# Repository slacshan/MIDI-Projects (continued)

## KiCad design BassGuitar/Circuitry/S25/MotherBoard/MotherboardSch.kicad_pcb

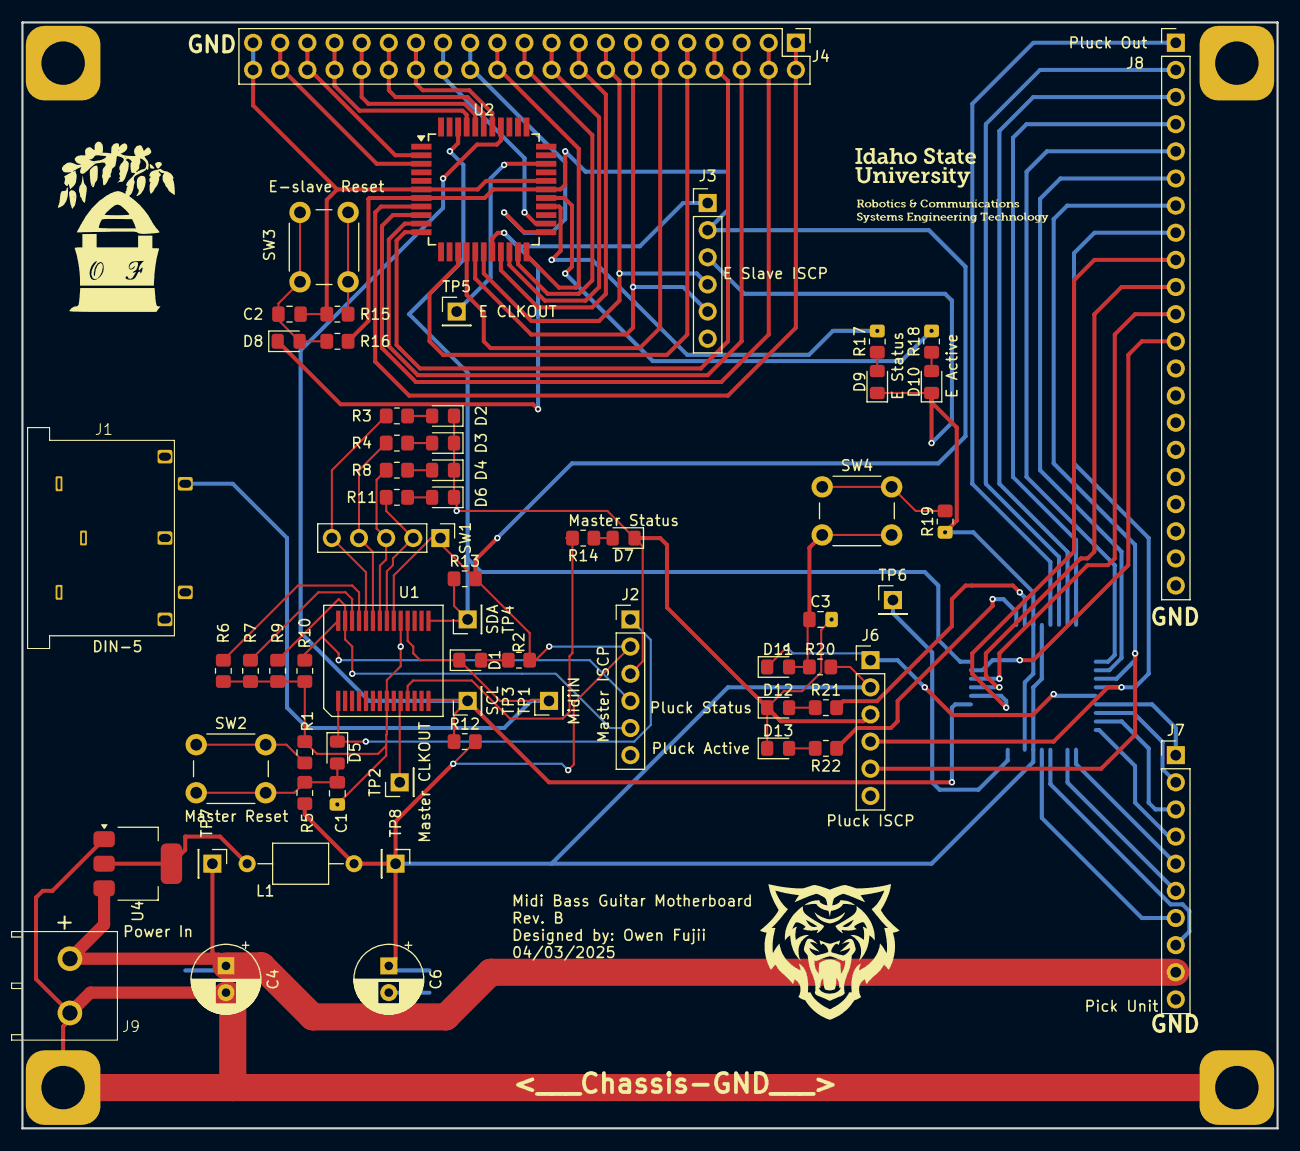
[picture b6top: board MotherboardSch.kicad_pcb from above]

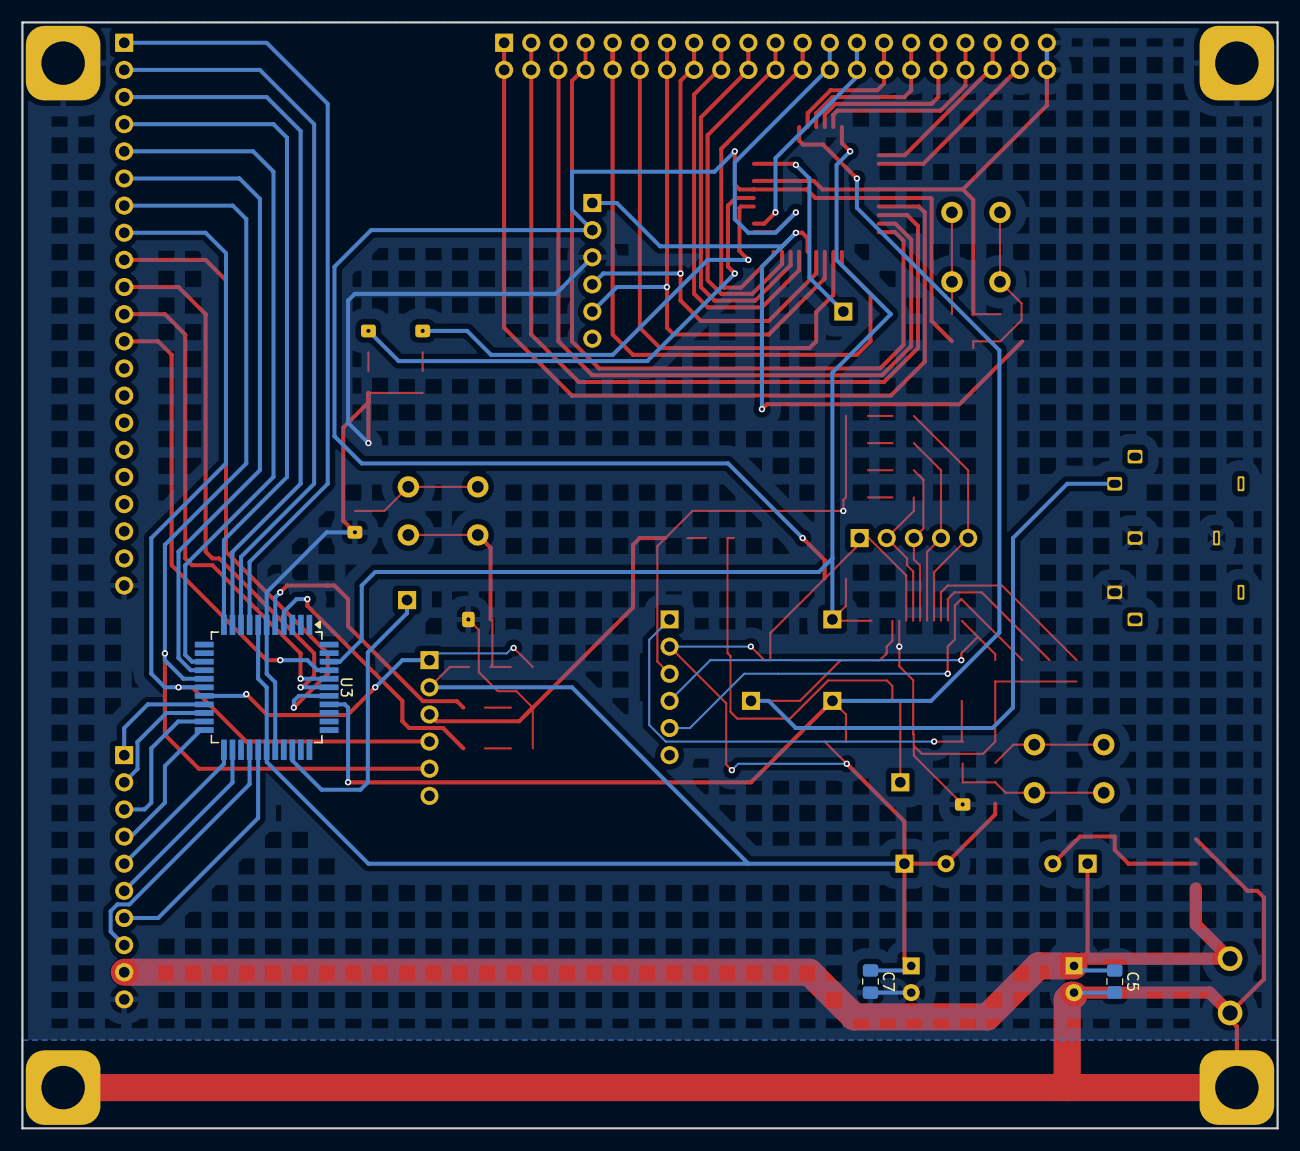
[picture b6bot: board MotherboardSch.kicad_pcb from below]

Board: 2 copper layers, 117.5 x 103.5 mm, 67 parts (3 on the bottom side), 83 nets.

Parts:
C1, C2, C3: 10uF; C_0805_2012Metric_Pad1.18x1.45mm_HandSolder
C4, C6: 100uF; CP_Radial_D6.3mm_P2.50mm
C5, C7: 0.1uF; C_0805_2012Metric_Pad1.18x1.45mm_HandSolder
D1: LED; D_0805_2012Metric_Pad1.15x1.40mm_HandSolder
D2: 8; D_0805_2012Metric_Pad1.15x1.40mm_HandSolder
D3: 4; D_0805_2012Metric_Pad1.15x1.40mm_HandSolder
D4: 2; D_0805_2012Metric_Pad1.15x1.40mm_HandSolder
D5, D8, D11: 4148; D_0805_2012Metric_Pad1.15x1.40mm_HandSolder
D6: 1; D_0805_2012Metric_Pad1.15x1.40mm_HandSolder
D7: Master Status; D_0805_2012Metric_Pad1.15x1.40mm_HandSolder
D9: E Status; D_0805_2012Metric_Pad1.15x1.40mm_HandSolder
D10: E Active; D_0805_2012Metric_Pad1.15x1.40mm_HandSolder
D12: Pluck Status; D_0805_2012Metric_Pad1.15x1.40mm_HandSolder
D13: Pluck Active; D_0805_2012Metric_Pad1.15x1.40mm_HandSolder
J1: DIN-5; Din_5 Connector
J2: Master ISCP; PinHeader_1x06_P2.54mm_Vertical
J3: E SLAVE ISCP; PinHeader_1x06_P2.54mm_Vertical
J4: E Slave Out; PinHeader_2x21_P2.54mm_Vertical
J6: Pluck ISCP; PinHeader_1x06_P2.54mm_Vertical
J7: Pick Unit; PinHeader_1x10_P2.54mm_Vertical
J8: Pluck Out; PinHeader_1x21_P2.54mm_Vertical
J9: Power In; Two_Pin_Screw_Terminal
L1: 10uH; L_Axial_L5.0mm_D3.6mm_P10.00mm_Horizontal_Murata_BL01RN1A2A2
R1, R15, R19: 10Ω; R_0805_2012Metric_Pad1.20x1.40mm_HandSolder
R2: 1kΩ; R_0805_2012Metric_Pad1.20x1.40mm_HandSolder
R3, R4, R8, R11, R14, R17, R18, R21, R22: 330Ω; R_0805_2012Metric_Pad1.20x1.40mm_HandSolder
R5, R6, R7, R9, R10, R16, R20: 10kΩ; R_0805_2012Metric_Pad1.20x1.40mm_HandSolder
R12, R13: 2.2kΩ; R_0805_2012Metric_Pad1.20x1.40mm_HandSolder
SW1: PinHeader_1x05_P2.54mm_Vertical
SW2: Master Reset; SW_PUSH_6mm_H5mm
SW3: E-slave Reset; SW_PUSH_6mm_H5mm
SW4: Pluck Reset; SW_PUSH_6mm_H5mm
TP1: MidiIN; PinHeader_1x01_P2.54mm_Vertical
TP2: Master CLKOUT; PinHeader_1x01_P2.54mm_Vertical
TP3: SCL; PinHeader_1x01_P2.54mm_Vertical
TP4: SDA; PinHeader_1x01_P2.54mm_Vertical
TP5: E CLKOUT; PinHeader_1x01_P2.54mm_Vertical
TP6: PLUCK CLKOUT; PinHeader_1x01_P2.54mm_Vertical
TP7: P-IN; PinHeader_1x01_P2.54mm_Vertical
TP8: 5v; PinHeader_1x01_P2.54mm_Vertical
U1: PIC16F1788; SSOP-28
U2, U3: PIC16F1789; TQFP-44_10x10mm_P0.8mm_Handsolder
U4: LM1117MP-1.8; SOT-223-3_TabPin2

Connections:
1: R11.2, SW1.2 (1), U1.21 (INT/AN12/RB0)
2: R8.2, SW1.3 (2), U1.22 (P1C/AN10/RB1)
4: R4.2, SW1.4, U1.23 (P1B/AN8/RB2)
8: R3.2, SW1.5 (8), U1.24 (PGM/C12IN2-/AN8/RB3)
+5v: C6.1, C7.1, J2.2, J3.2, J6.2, L1.2, R2.2, R5.2, R12.2, R13.2, R16.2, R20.2, SW1.1 (Com), TP8.1, U1.20 (VDD), U2.7 (Vdd), U2.28 (Vdd), U3.7 (Vdd), U3.28 (Vdd)
+12v: C4.1, C5.1, J7.9, J9.1, TP7.1, U4.3 (VI)
/String Strike Slave/A0: J8.3, U3.10 (RB2/AN8/OPA2IN-/DAC3OUT1)
/String Strike Slave/A1: J8.4, U3.11 (RB3/AN9/CXNI2-/CCP2)
/String Strike Slave/A MUTE: J8.10, U3.39 (RD1/CxIN4-/OPA3OUT)
/String Strike Slave/D0: J8.5, U3.14 (RB4/AN11/C3IN1+)
/String Strike Slave/D1: J8.6, U3.15 (RB5/AN13/C4IN2-/CCP3)
/String Strike Slave/D MUTE: J8.11, U3.40 (RD2/OPA3IN-/DAC4OUT1)
/String Strike Slave/E0: J8.1, U3.8 (RB0/AN12/CCP1/C2IN1+)
/String Strike Slave/E1: J8.2, U3.9 (RB1/AN10/CxIN3-/OPA2OUT)
/String Strike Slave/E MUTE: J8.9, U3.38 (RD0/OPA3IN+)
/String Strike Slave/G MUTE: J8.12, U3.41 (RD3/PSMC4A)
A1: J4.5, U2.14 (RB4/AN11/C3IN1+)
A2: J4.17, U2.40 (RD2/OPA3IN-/DAC4OUT1)
A#1: J4.6, U2.15 (RB5/AN13/C4IN2-/CCP3)
A#2: J4.18, U2.41 (RD3/PSMC4A)
B1: J3.5, J4.7, U2.16 (RB6/C4IN1+/ICSPCLK)
B2: J4.19, U2.2 (RD4/PSM3F)
C2: J3.4, J4.8, U2.17 (RB7/DACxOUT2-/ICSPDAT)
C3: J4.20, U2.3 (RD5/PSMC3E)
C#2: J4.9, U2.19 (RA0/AN0/CxIN0-)
D2: J4.10, U2.20 (RA1/AN1/CxIN1-/OPA1OUT)
D#2: J4.11, U2.21 (RA2/AN2/CxIN0+/DAC1OUT1)
E2: J4.12, U2.22 (RA3/AN3/VREF+/C1IN1+)
Earth_GND: C4.2, C5.2, J9.2, U4.1 (GND)
F1: J4.1, U2.8 (RB0/AN12/CCP1/C2IN1+)
F2: J4.13, U2.23 (RA4/C1OUT/OPA1IN+/T0CKI)
F#1: J4.2, U2.9 (RB1/AN10/CxIN3-/OPA2OUT)
F#2: J4.14, U2.24 (RA5/AN4/C2OUT/OPA1IN+)
G1: J4.3, U2.10 (RB2/AN8/OPA2IN-/DAC3OUT1)
G2: J4.15, U2.38 (RD0/OPA3IN+)
G#1: J4.4, U2.11 (RB3/AN9/CXNI2-/CCP2)
G#2: J4.16, U2.39 (RD1/CxIN4-/OPA3OUT)
GND: C1.2, C2.2, C3.2, C6.2, C7.2, D2.1 (K), D3.1 (K), D4.1 (K), D6.1 (K), D7.1 (K), D9.1 (K), D10.1 (K), D12.1 (K), D13.1 (K), J1.2, J1.4, J1.6, J2.3, J3.3, J4.21, J6.3, J7.10, J8.21, R1.1, R6.1, R7.1, R9.1, R10.1, R15.1, R19.1, U1.8 (VSS), U1.19 (VSS), U2.6 (Vss), U2.29 (Vss), U3.6 (Vss), U3.29 (Vss)
I2Cclk: R12.1, TP3.1, U1.14 (RC3/SCK/SCL), U2.37 (RC3/SCL/SCK/PSMC1D), U3.37 (RC3/SCL/SCK/PSMC1D)
I2Cdat: R13.1, TP4.1, U1.15 (RC4/SDI/SDA), U2.42 (RC4/SDI/SDA/PSMC1E), U3.42 (RC4/SDI/SDA/PSMC1E)
MSCLR E: D8.1, J3.1, U2.18 (Vpp/~MCLR/RE3)
MSCLR P: D11.1, J6.1, U3.18 (Vpp/~MCLR/RE3)
unnamed: C1.1, D5.2, R5.1, SW2.2
unnamed: C2.1, D8.2, R16.1, SW3.2
unnamed: C3.1, D11.2, R20.1, SW4.2
unnamed: D1.2 (A), R2.1
unnamed: D1.1 (K), J1.5, TP1.1, U1.18 (RC7/RX/DT)
unnamed: D2.2 (A), R3.1
unnamed: D3.2 (A), R4.1
unnamed: D4.2 (A), R8.1
unnamed: D6.2 (A), R11.1
unnamed: D7.2 (A), R14.1
unnamed: D9.2 (A), R17.1
unnamed: D10.2 (A), R18.1
unnamed: D12.2 (A), R21.1
unnamed: D13.2 (A), R22.2
unnamed: R1.2, SW2.1
unnamed: R15.2, SW3.1
unnamed: R19.2, SW4.1
unnamed: TP2.1, U1.10 (CLKOUT/OSC2/RA6)
unnamed: R6.2, U1.25 (P1D/AN11/RB4)
unnamed: R14.2, U1.11 (RC0/T1OSO/T1CK1)
unnamed: D5.1, J2.1, U1.1 (RE3/~MCLR/Vpp)
unnamed: R7.2, U1.26 (~T1G/AN13/RB5)
unnamed: TP5.1, U2.31 (RA6/C2OUT/CLKOUT)
unnamed: R17.2, U2.26 (RE1/AN6/PSMC3B)
unnamed: R18.2, U2.27 (RE2/AN7/PSMC3A)
unnamed: J7.1, U3.19 (RA0/AN0/CxIN0-)
unnamed: J7.2, U3.20 (RA1/AN1/CxIN1-/OPA1OUT)
unnamed: J7.3, U3.21 (RA2/AN2/CxIN0+/DAC1OUT1)
unnamed: J7.4, U3.22 (RA3/AN3/VREF+/C1IN1+)
unnamed: J7.5, U3.23 (RA4/C1OUT/OPA1IN+/T0CKI)
unnamed: J7.6, U3.24 (RA5/AN4/C2OUT/OPA1IN+)
unnamed: TP6.1, U3.31 (RA6/C2OUT/CLKOUT)
unnamed: R22.1, U3.4 (RD6/PSMC3D)
unnamed: R21.2, U3.5 (RD7/C4OUT/PSMC3C)
unnamed: J7.8, U3.26 (RE1/AN6/PSMC3B)
unnamed: J7.7, U3.27 (RE2/AN7/PSMC3A)
unnamed: L1.1, U4.2 (VO)
RB6 P: J6.5, J8.7, U3.16 (RB6/C4IN1+/ICSPCLK)
RB6M: J2.5, R9.2, U1.27 (ICSPCLK/RB6)
RB7 P: J6.4, J8.8, U3.17 (RB7/DACxOUT2-/ICSPDAT)
RB7M: J2.4, R10.2, U1.28 (ICSPDAT/RB7)

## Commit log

2025-11-19 proper gitnore naming
2025-11-19 initial file uploads
2025-12-01 updating files
2025-12-03 added the master code I have been working on.
2025-12-03 added the slave code for I2C 3 byte recive.
2025-12-04 Untracked files in the gitignore and updated the master code to now recive midi and send it via I2C. It still need to be formated and made to work with the 2 dip switches.
2025-12-05 master has code to filter by channel and I am currently working on getting the note filter to work now. -Payden
2025-12-06 added afew files to the git ignore and changed a test bit in the master code. -payden
2025-12-08 week 7s work and updating hours
2025-12-08 no longer using filter file, still working on the note filter. -payden
2025-12-09 possibly fixed the note filter but need to test and verify its operation. -payden
2025-12-09 added my flowchart for the master code. -Payden
2025-12-09 updated hours
2025-12-10 new pcb mounting plate
2025-12-12 slave code that now works. -payden
2025-12-12 added the slave code that works with one byte. -Payden
2025-12-12 slightly changed master code. -Payden
2025-12-12 random files. -Payden
2025-12-16 updated cad files and hours
2025-12-16 made BOM
2025-12-17 fixed master issues. -Payden
2025-12-17 changed a few things on master to make it more reliable. -Payden
2025-12-17 added jasons and brandons slave code, added time sheets and test songs. -Payden
2025-12-18 made pdfs for final report
2025-12-18 final report added
2025-12-19 issues. -payden
2025-12-19 Unborking the Master files. -Payden
2025-12-19 Removing the borked files. -Payden
